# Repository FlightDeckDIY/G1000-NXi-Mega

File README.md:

### G1000-NXi-Mega

# G1000 NXi with an integrated Arduino Mega for Flight Simulators

Welcome to the G1000 NXi Mega project! This repository contains the schematic and PCB design files for a custom-built G1000 avionics panel, designed specifically for use with flight simulators like Microsoft Flight Simulator and X-Plane. Using MobiFlight to connect the G1000 hardware to your simulator of choice.

## Features
- Fully functional G1000 avionics system designed for flight simulation enthusiasts and student pilots.
- Integrated Arduino Mega for simplified connections and functionality.
- Open-source schematic and PCB designs for easy replication and modification.
- Compatible with Microsoft Flight Simulator and X-Plane.

## Getting Started
To get started with the G1000 NXi Mega:
1. Download the schematic and PCB files from the `design` folder.
2. Review the build documentation in the `docs` folder.
3. Use the included Gerber files to order PCBs from your preferred manufacturer.
4. Follow the assembly instructions to build your own G1000 avionics panel.

### Prerequisites
- Basic knowledge of electronics and PCB assembly.
- Access to a 3D printer (if building the enclosure).
- Arduino IDE and a spare Arduino for programming the Arduino Mega.

## Documentation
- **Schematics**: [View Schematics](./G1000-NXi-Mega/Frame%20PCBs)
- **3D Models**: [View Enclosure Models](https://cad.onshape.com/documents/151676533be7f9dde157788c/w/2f40da56e230263b51d6582b/e/3766505c1afa7c69551d04a4)
- **Build Guide**: Not created yet

## How to Contribute
We welcome contributions! Here's how you can get involved:
1. Fork this repository.
2. Make your changes in a new branch.
3. Submit a pull request with a description of your changes.

## License
This project is licensed under the [Creative Commons Attribution-NonCommercial 4.0 International License](https://creativecommons.org/licenses/by-nc/4.0/).

### License Summary
- **You are free to**:
  - Share — copy and redistribute the material in any medium or format.
  - Adapt — remix, transform, and build upon the material.
- **Under the following terms**:
  - Attribution — You must give appropriate credit, provide a link to the license, and indicate if changes were made.
  - NonCommercial — You may not use the material for commercial purposes.

For more details, see the full license text in the `LICENSE` file.

## Support
If you encounter any issues or have questions about the project, feel free to open an issue or contact me directly through the GitHub discussions page.

## Acknowledgments
Special thanks to the flight simulation and open-source hardware communities for their support and inspiration!

---

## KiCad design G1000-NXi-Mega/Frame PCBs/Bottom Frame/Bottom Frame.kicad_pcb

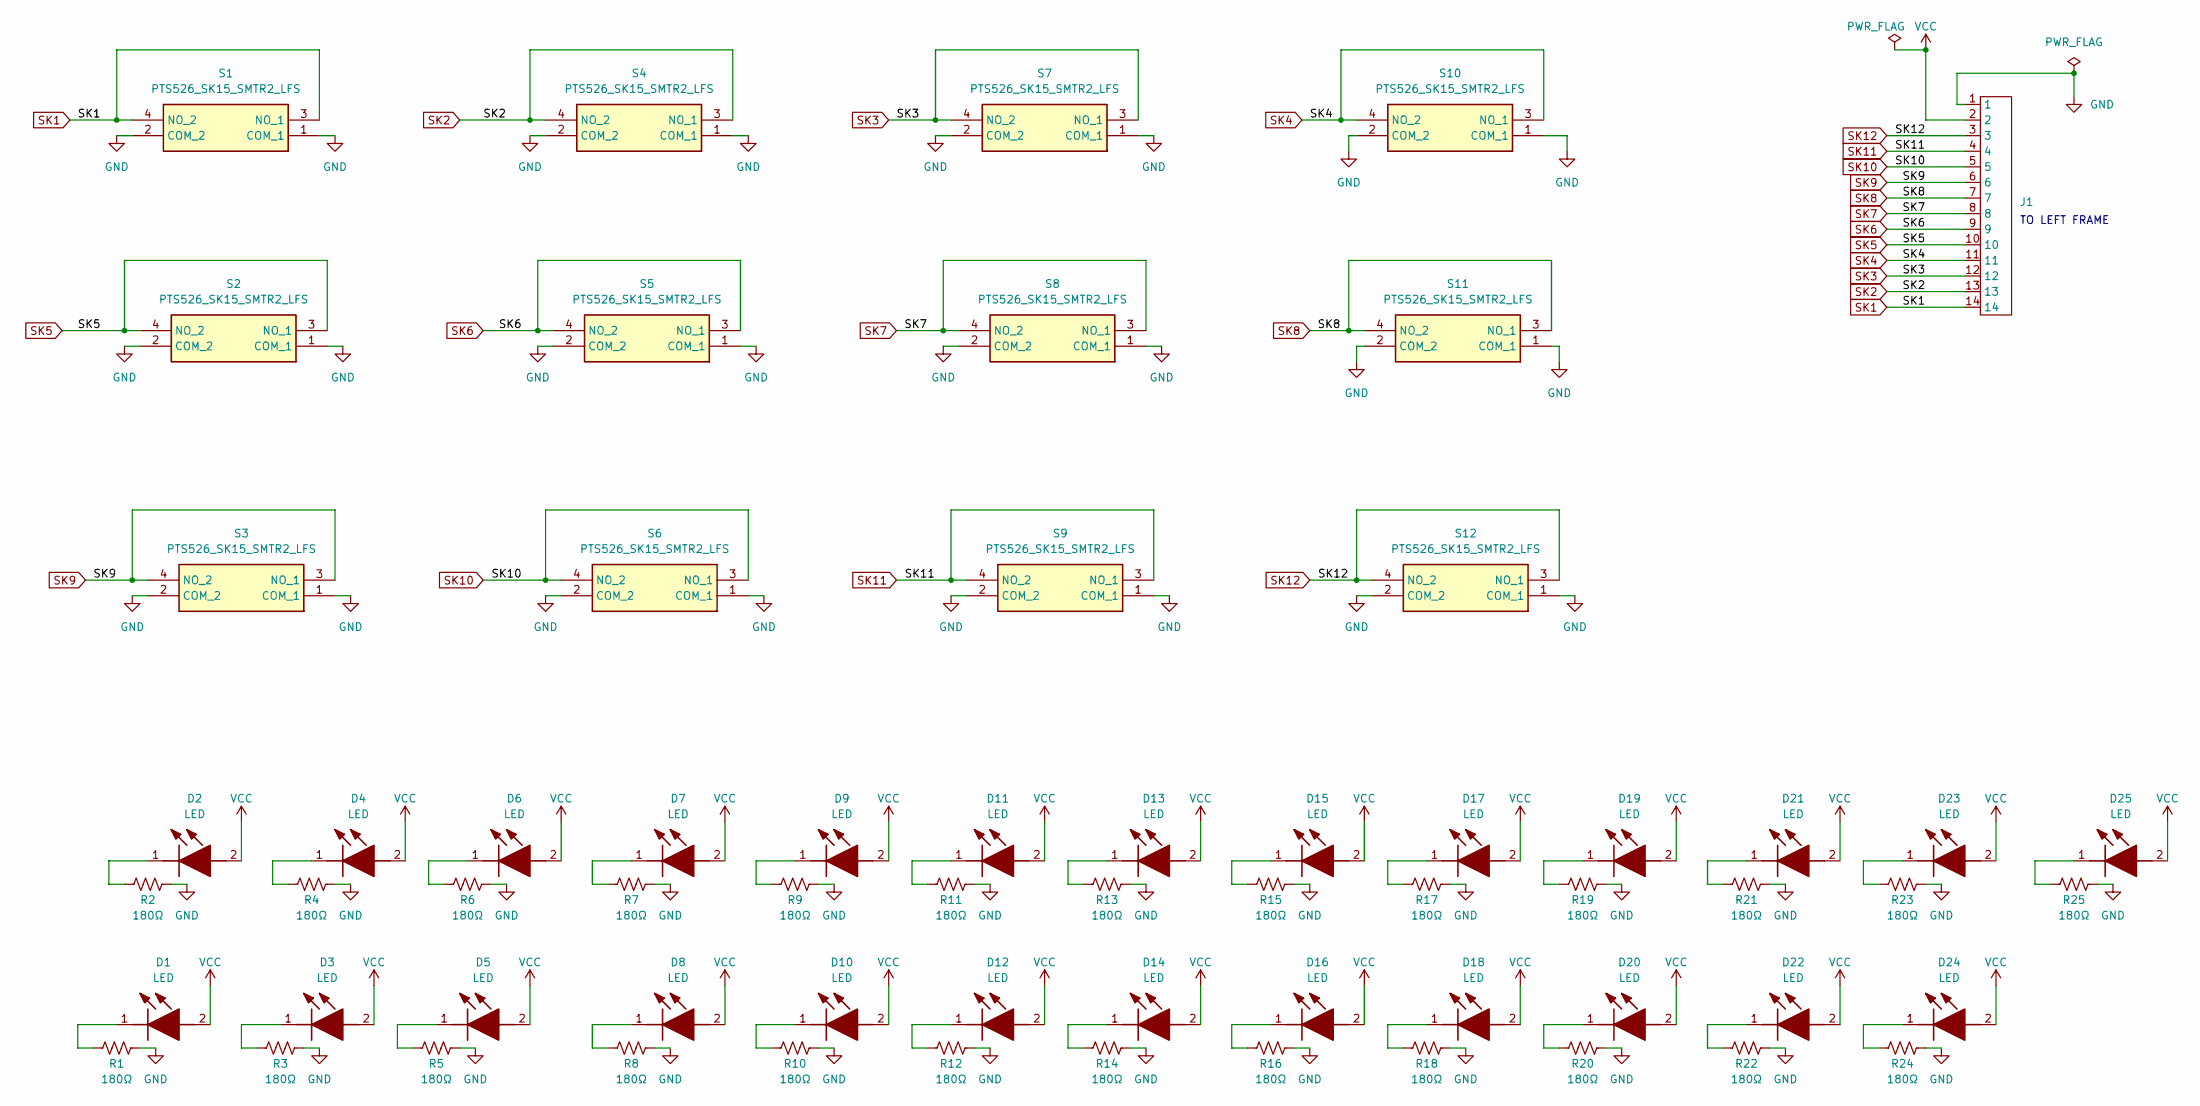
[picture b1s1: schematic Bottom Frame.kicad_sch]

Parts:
D1, D2, D3, D4, D5, D6, D7, D8, D9, D10, D11, D12, D13, D14, D15, D16, D17, D18, D19, D20, D21, D22, D23, D24, D25: LED; LEDC1608X39N; Mouser Part Number 743-IN-S63AT5UW
J1: CF31141D0R0-05-NH
R1, R2, R3, R4, R5, R6, R7, R8, R9, R10, R11, R12, R13, R14, R15, R16, R17, R18, R19, R20, R21, R22, R23, R24, R25: 180Ω; R_0603_1608Metric_Pad0.98x0.95mm_HandSolder
S1, S2, S3, S4, S5, S6, S7, S8, S9, S10, S11, S12: PTS526_SK15_SMTR2_LFS; PTS526SK15SMTR2LFS; Mouser Part Number 611-PTS526SK15SMR2L

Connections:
GND: J1.1, R1.2, R2.2, R3.2, R4.2, R5.2, R6.2, R7.2, R8.2, R9.2, R10.2, R11.2, R12.2, R13.2, R14.2, R15.2, R16.2, R17.2, R18.2, R19.2, R20.2, R21.2, R22.2, R23.2, R24.2, R25.2, S1.1 (COM_1), S1.2 (COM_2), S2.1 (COM_1), S2.2 (COM_2), S3.1 (COM_1), S3.2 (COM_2), S4.1 (COM_1), S4.2 (COM_2), S5.1 (COM_1), S5.2 (COM_2), S6.1 (COM_1), S6.2 (COM_2), S7.1 (COM_1), S7.2 (COM_2), S8.1 (COM_1), S8.2 (COM_2), S9.1 (COM_1), S9.2 (COM_2), S10.1 (COM_1), S10.2 (COM_2), S11.1 (COM_1), S11.2 (COM_2), S12.1 (COM_1), S12.2 (COM_2)
unnamed: D1.1 (K), R1.1
unnamed: D2.1 (K), R2.1
unnamed: D3.1 (K), R3.1
unnamed: D4.1 (K), R4.1
unnamed: D5.1 (K), R5.1
unnamed: D6.1 (K), R6.1
unnamed: D7.1 (K), R7.1
unnamed: D8.1 (K), R8.1
unnamed: D9.1 (K), R9.1
unnamed: D10.1 (K), R10.1
unnamed: D11.1 (K), R11.1
unnamed: D12.1 (K), R12.1
unnamed: D13.1 (K), R13.1
unnamed: D14.1 (K), R14.1
unnamed: D15.1 (K), R15.1
unnamed: D16.1 (K), R16.1
unnamed: D17.1 (K), R17.1
unnamed: D18.1 (K), R18.1
unnamed: D19.1 (K), R19.1
unnamed: D20.1 (K), R20.1
unnamed: D21.1 (K), R21.1
unnamed: D22.1 (K), R22.1
unnamed: D23.1 (K), R23.1
unnamed: D24.1 (K), R24.1
unnamed: D25.1 (K), R25.1
SK1: J1.14, S1.3 (NO_1), S1.4 (NO_2)
SK2: J1.13, S4.3 (NO_1), S4.4 (NO_2)
SK3: J1.12, S7.3 (NO_1), S7.4 (NO_2)
SK4: J1.11, S10.3 (NO_1), S10.4 (NO_2)
SK5: J1.10, S2.3 (NO_1), S2.4 (NO_2)
SK6: J1.9, S5.3 (NO_1), S5.4 (NO_2)
SK7: J1.8, S8.3 (NO_1), S8.4 (NO_2)
SK8: J1.7, S11.3 (NO_1), S11.4 (NO_2)
SK9: J1.6, S3.3 (NO_1), S3.4 (NO_2)
SK10: J1.5, S6.3 (NO_1), S6.4 (NO_2)
SK11: J1.4, S9.3 (NO_1), S9.4 (NO_2)
SK12: J1.3, S12.3 (NO_1), S12.4 (NO_2)
VCC: D1.2 (A), D2.2 (A), D3.2 (A), D4.2 (A), D5.2 (A), D6.2 (A), D7.2 (A), D8.2 (A), D9.2 (A), D10.2 (A), D11.2 (A), D12.2 (A), D13.2 (A), D14.2 (A), D15.2 (A), D16.2 (A), D17.2 (A), D18.2 (A), D19.2 (A), D20.2 (A), D21.2 (A), D22.2 (A), D23.2 (A), D24.2 (A), D25.2 (A), J1.2

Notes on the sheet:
TO LEFT FRAME

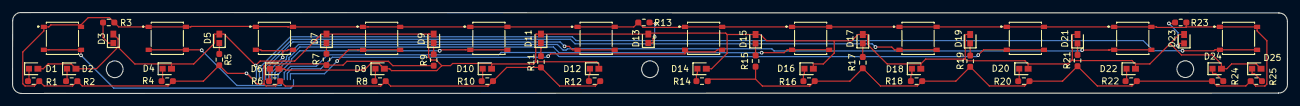
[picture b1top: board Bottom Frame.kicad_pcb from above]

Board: 2 copper layers, 206.0 x 13.1 mm, 66 parts (1 on the bottom side), 39 nets.

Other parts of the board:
C: MountingHole_2.7mm_M2.5
L: MountingHole_2.7mm_M2.5
R: MountingHole_2.7mm_M2.5

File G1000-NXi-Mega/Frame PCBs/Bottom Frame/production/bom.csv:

Designator,Footprint,Quantity,Value,LCSC Part #
"D1, D10, D11, D12, D13, D14, D15, D16, D17, D18, D19, D2, D20, D21, D22, D23, D24, D25, D3, D4, D5, D6, D7, D8, D9",LEDC1608X39N,25,LED,
J1,CF31141D0R0-05-NH,1,~,
"R1, R10, R11, R12, R13, R14, R15, R16, R17, R18, R19, R2, R20, R21, R22, R23, R24, R25, R3, R4, R5, R6, R7, R8, R9",0603,25,180Ω,
"S1, S10, S11, S12, S2, S3, S4, S5, S6, S7, S8, S9",PTS526SK15SMTR2LFS,12,PTS526_SK15_SMTR2_LFS,

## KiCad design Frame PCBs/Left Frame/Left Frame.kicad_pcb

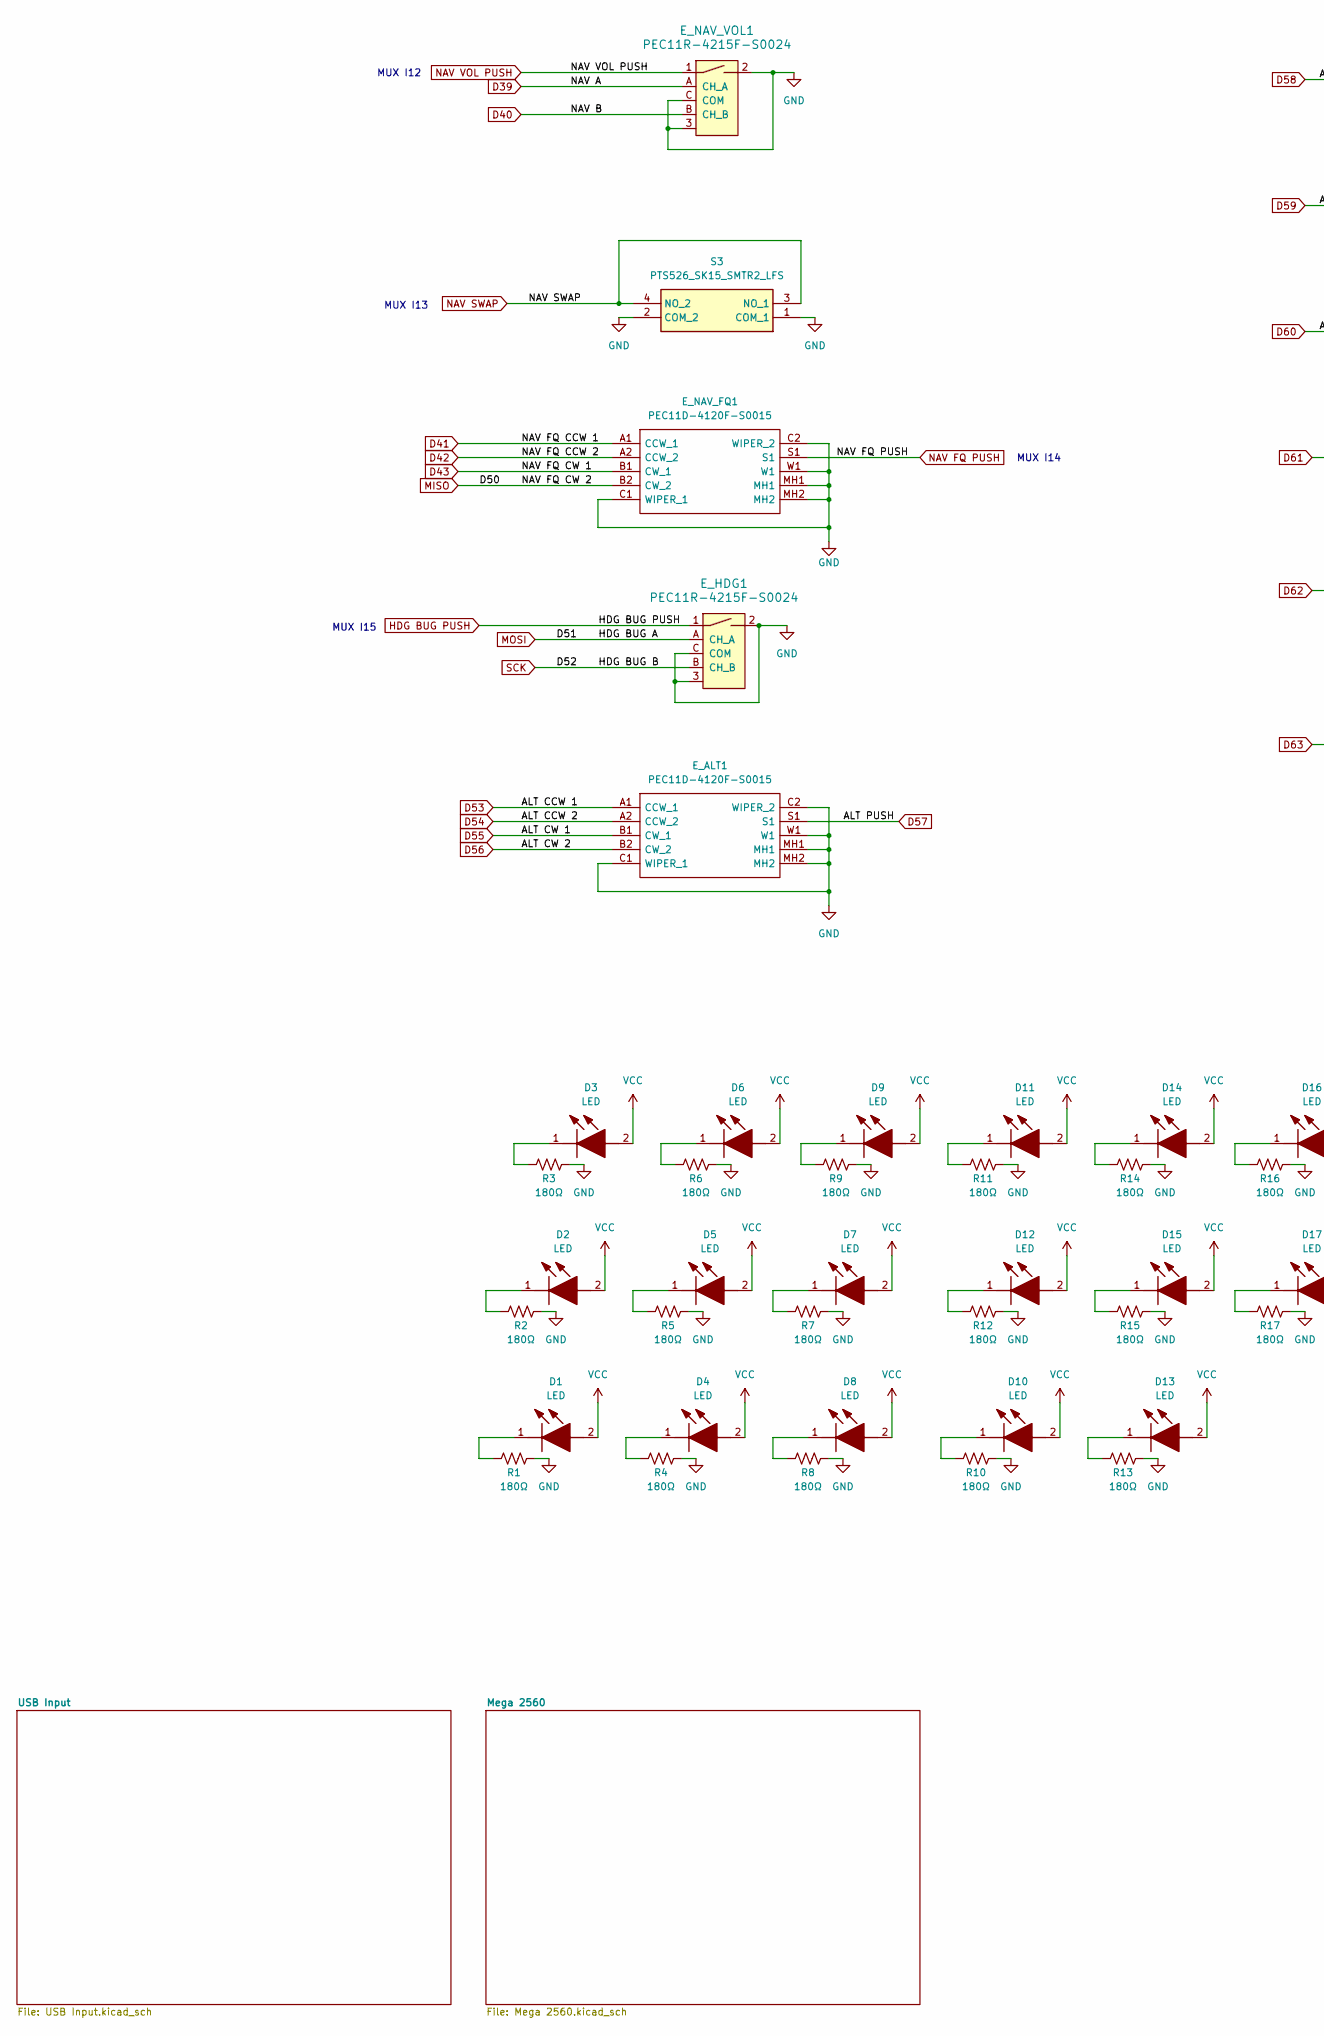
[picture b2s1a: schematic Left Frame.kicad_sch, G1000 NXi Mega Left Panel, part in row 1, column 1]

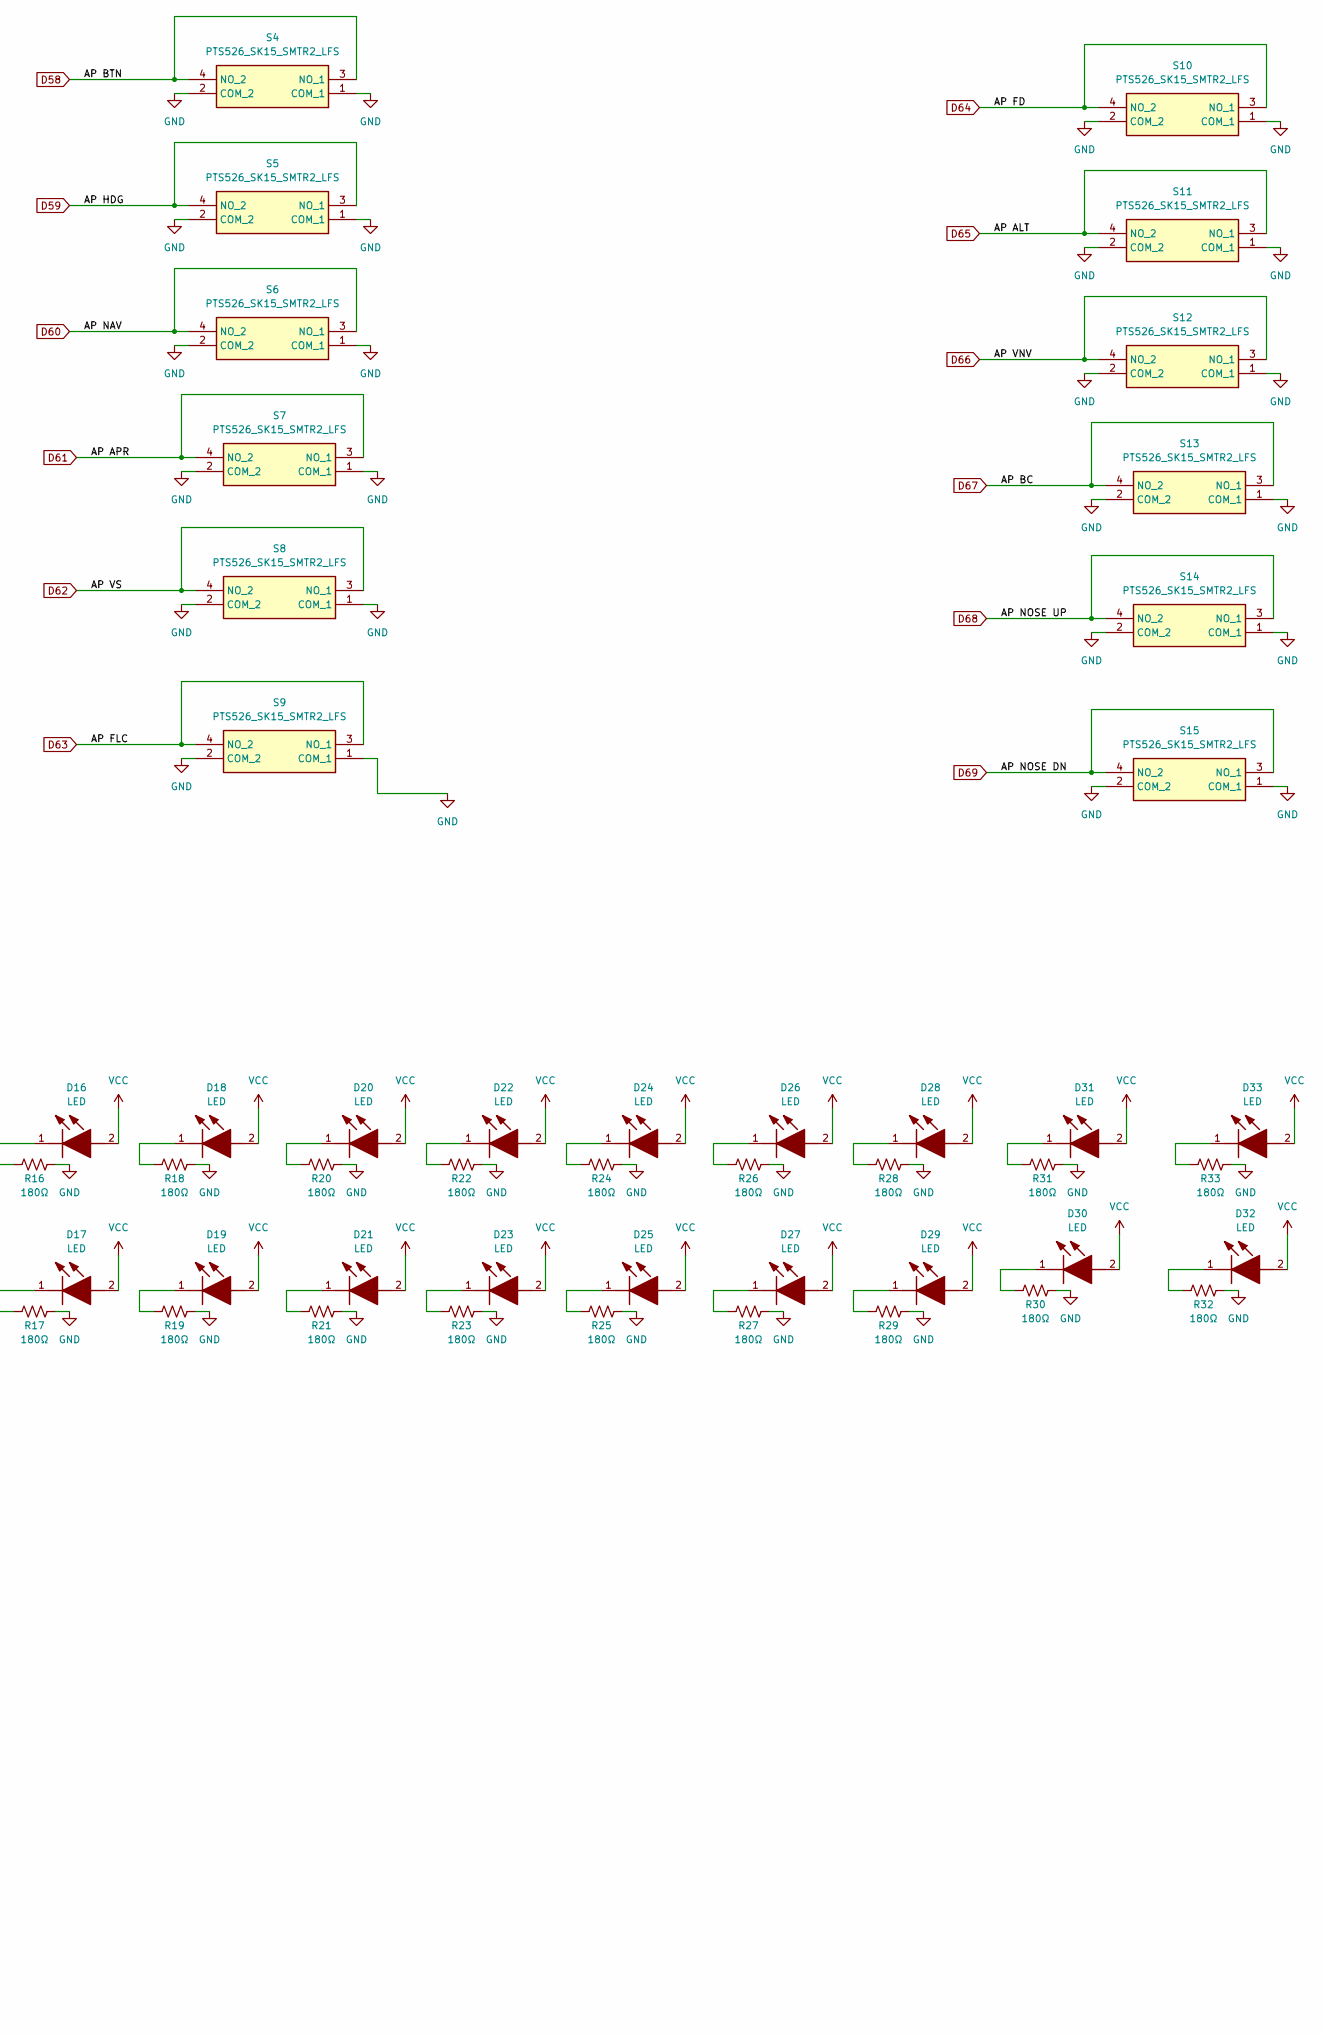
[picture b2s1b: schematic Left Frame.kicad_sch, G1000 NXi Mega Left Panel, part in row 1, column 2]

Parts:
D1, D2, D3, D4, D5, D6, D7, D8, D9, D10, D11, D12, D13, D14, D15, D16, D17, D18, D19, D20, D21, D22, D23, D24, D25, D26, D27, D28, D29, D30, D31, D32, D33: LED; LEDC1608X39N; Mouser Part Number 743-IN-S63AT5UW
E_ALT1: PEC11D-4120F-S0015; PEC11D4120FS0015; Mouser Part Number 652-PEC11D4120FS0015
E_HDG1: PEC11R-4215F-S0024; Rotary_Encoder_Switched_PEC11R; MPN PEC11R-4215F-S0024; Digi-Key_PN PEC11R-4215F-S0024-ND
E_NAV_FQ1: PEC11D-4120F-S0015; PEC11D4120FS0015; Mouser Part Number 652-PEC11D4120FS0015
E_NAV_VOL1: PEC11R-4215F-S0024; Rotary_Encoder_Switched_PEC11R; MPN PEC11R-4215F-S0024; Digi-Key_PN PEC11R-4215F-S0024-ND
R1, R2, R3, R4, R5, R6, R7, R8, R9, R10, R11, R12, R13, R14, R15, R16, R17, R18, R19, R20, R21, R22, R23, R24, R25, R26, R27, R28, R29, R30, R31, R32, R33: 180Ω; R_0603_1608Metric_Pad0.98x0.95mm_HandSolder
S3, S4, S5, S6, S7, S8, S9, S10, S11, S12, S13, S14, S15: PTS526_SK15_SMTR2_LFS; PTS526SK15SMTR2LFS; Mouser Part Number 611-PTS526SK15SMR2L

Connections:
D39: E_NAV_VOL1.A (CH_A); also elsewhere on the board
D40: E_NAV_VOL1.B (CH_B); also elsewhere on the board
D41: E_NAV_FQ1.A1 (CCW_1); also elsewhere on the board
D42: E_NAV_FQ1.A2 (CCW_2); also elsewhere on the board
D43: E_NAV_FQ1.B1 (CW_1); also elsewhere on the board
D53: E_ALT1.A1 (CCW_1); also elsewhere on the board
D54: E_ALT1.A2 (CCW_2); also elsewhere on the board
D55: E_ALT1.B1 (CW_1); also elsewhere on the board
D56: E_ALT1.B2 (CW_2); also elsewhere on the board
D57: E_ALT1.S1; also elsewhere on the board
D58: S4.3 (NO_1), S4.4 (NO_2); also elsewhere on the board
D59: S5.3 (NO_1), S5.4 (NO_2); also elsewhere on the board
D60: S6.3 (NO_1), S6.4 (NO_2); also elsewhere on the board
D61: S7.3 (NO_1), S7.4 (NO_2); also elsewhere on the board
D62: S8.3 (NO_1), S8.4 (NO_2); also elsewhere on the board
D63: S9.3 (NO_1), S9.4 (NO_2); also elsewhere on the board
D64: S10.3 (NO_1), S10.4 (NO_2); also elsewhere on the board
D65: S11.3 (NO_1), S11.4 (NO_2); also elsewhere on the board
D66: S12.3 (NO_1), S12.4 (NO_2); also elsewhere on the board
D67: S13.3 (NO_1), S13.4 (NO_2); also elsewhere on the board
D68: S14.3 (NO_1), S14.4 (NO_2); also elsewhere on the board
D69: S15.3 (NO_1), S15.4 (NO_2); also elsewhere on the board
GND: E_ALT1.C1 (WIPER_1), E_ALT1.C2 (WIPER_2), E_ALT1.MH1, E_ALT1.MH2, E_ALT1.W1, E_HDG1.2, E_HDG1.3, E_HDG1.C (COM), E_NAV_FQ1.C1 (WIPER_1), E_NAV_FQ1.C2 (WIPER_2), E_NAV_FQ1.MH1, E_NAV_FQ1.MH2, E_NAV_FQ1.W1, E_NAV_VOL1.2, E_NAV_VOL1.3, E_NAV_VOL1.C (COM), R1.2, R2.2, R3.2, R4.2, R5.2, R6.2, R7.2, R8.2, R9.2, R10.2, R11.2, R12.2, R13.2, R14.2, R15.2, R16.2, R17.2, R18.2, R19.2, R20.2, R21.2, R22.2, R23.2, R24.2, R25.2, R26.2, R27.2, R28.2, R29.2, R30.2, R31.2, R32.2, R33.2, S3.1 (COM_1), S3.2 (COM_2), S4.1 (COM_1), S4.2 (COM_2), S5.1 (COM_1), S5.2 (COM_2), S6.1 (COM_1), S6.2 (COM_2), S7.1 (COM_1), S7.2 (COM_2), S8.1 (COM_1), S8.2 (COM_2), S9.1 (COM_1), S9.2 (COM_2), S10.1 (COM_1), S10.2 (COM_2), S11.1 (COM_1), S11.2 (COM_2), S12.1 (COM_1), S12.2 (COM_2), S13.1 (COM_1), S13.2 (COM_2), S14.1 (COM_1), S14.2 (COM_2), S15.1 (COM_1), S15.2 (COM_2); also elsewhere on the board
HDG BUG PUSH: E_HDG1.1; also elsewhere on the board
MISO: E_NAV_FQ1.B2 (CW_2); also elsewhere on the board
MOSI: E_HDG1.A (CH_A); also elsewhere on the board
NAV FQ PUSH: E_NAV_FQ1.S1; also elsewhere on the board
NAV SWAP: S3.3 (NO_1), S3.4 (NO_2); also elsewhere on the board
NAV VOL PUSH: E_NAV_VOL1.1; also elsewhere on the board
unnamed: D1.1 (K), R1.1
unnamed: D2.1 (K), R2.1
unnamed: D3.1 (K), R3.1
unnamed: D4.1 (K), R4.1
unnamed: D5.1 (K), R5.1
unnamed: D6.1 (K), R6.1
unnamed: D7.1 (K), R7.1
unnamed: D8.1 (K), R8.1
unnamed: D9.1 (K), R9.1
unnamed: D10.1 (K), R10.1
unnamed: D11.1 (K), R11.1
unnamed: D12.1 (K), R12.1
unnamed: D13.1 (K), R13.1
unnamed: D14.1 (K), R14.1
unnamed: D15.1 (K), R15.1
unnamed: D16.1 (K), R16.1
unnamed: D17.1 (K), R17.1
unnamed: D18.1 (K), R18.1
unnamed: D19.1 (K), R19.1
unnamed: D20.1 (K), R20.1
unnamed: D21.1 (K), R21.1
unnamed: D22.1 (K), R22.1
unnamed: D23.1 (K), R23.1
unnamed: D24.1 (K), R24.1
unnamed: D25.1 (K), R25.1
unnamed: D26.1 (K), R26.1
unnamed: D27.1 (K), R27.1
unnamed: D28.1 (K), R28.1
unnamed: D29.1 (K), R29.1
unnamed: D30.1 (K), R30.1
unnamed: D31.1 (K), R31.1
unnamed: D32.1 (K), R32.1
unnamed: D33.1 (K), R33.1
SCK: E_HDG1.B (CH_B); also elsewhere on the board
VCC: D1.2 (A), D2.2 (A), D3.2 (A), D4.2 (A), D5.2 (A), D6.2 (A), D7.2 (A), D8.2 (A), D9.2 (A), D10.2 (A), D11.2 (A), D12.2 (A), D13.2 (A), D14.2 (A), D15.2 (A), D16.2 (A), D17.2 (A), D18.2 (A), D19.2 (A), D20.2 (A), D21.2 (A), D22.2 (A), D23.2 (A), D24.2 (A), D25.2 (A), D26.2 (A), D27.2 (A), D28.2 (A), D29.2 (A), D30.2 (A), D31.2 (A), D32.2 (A), D33.2 (A); also elsewhere on the board

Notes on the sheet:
MUX I14
MUX I12
MUX I15
MUX I13

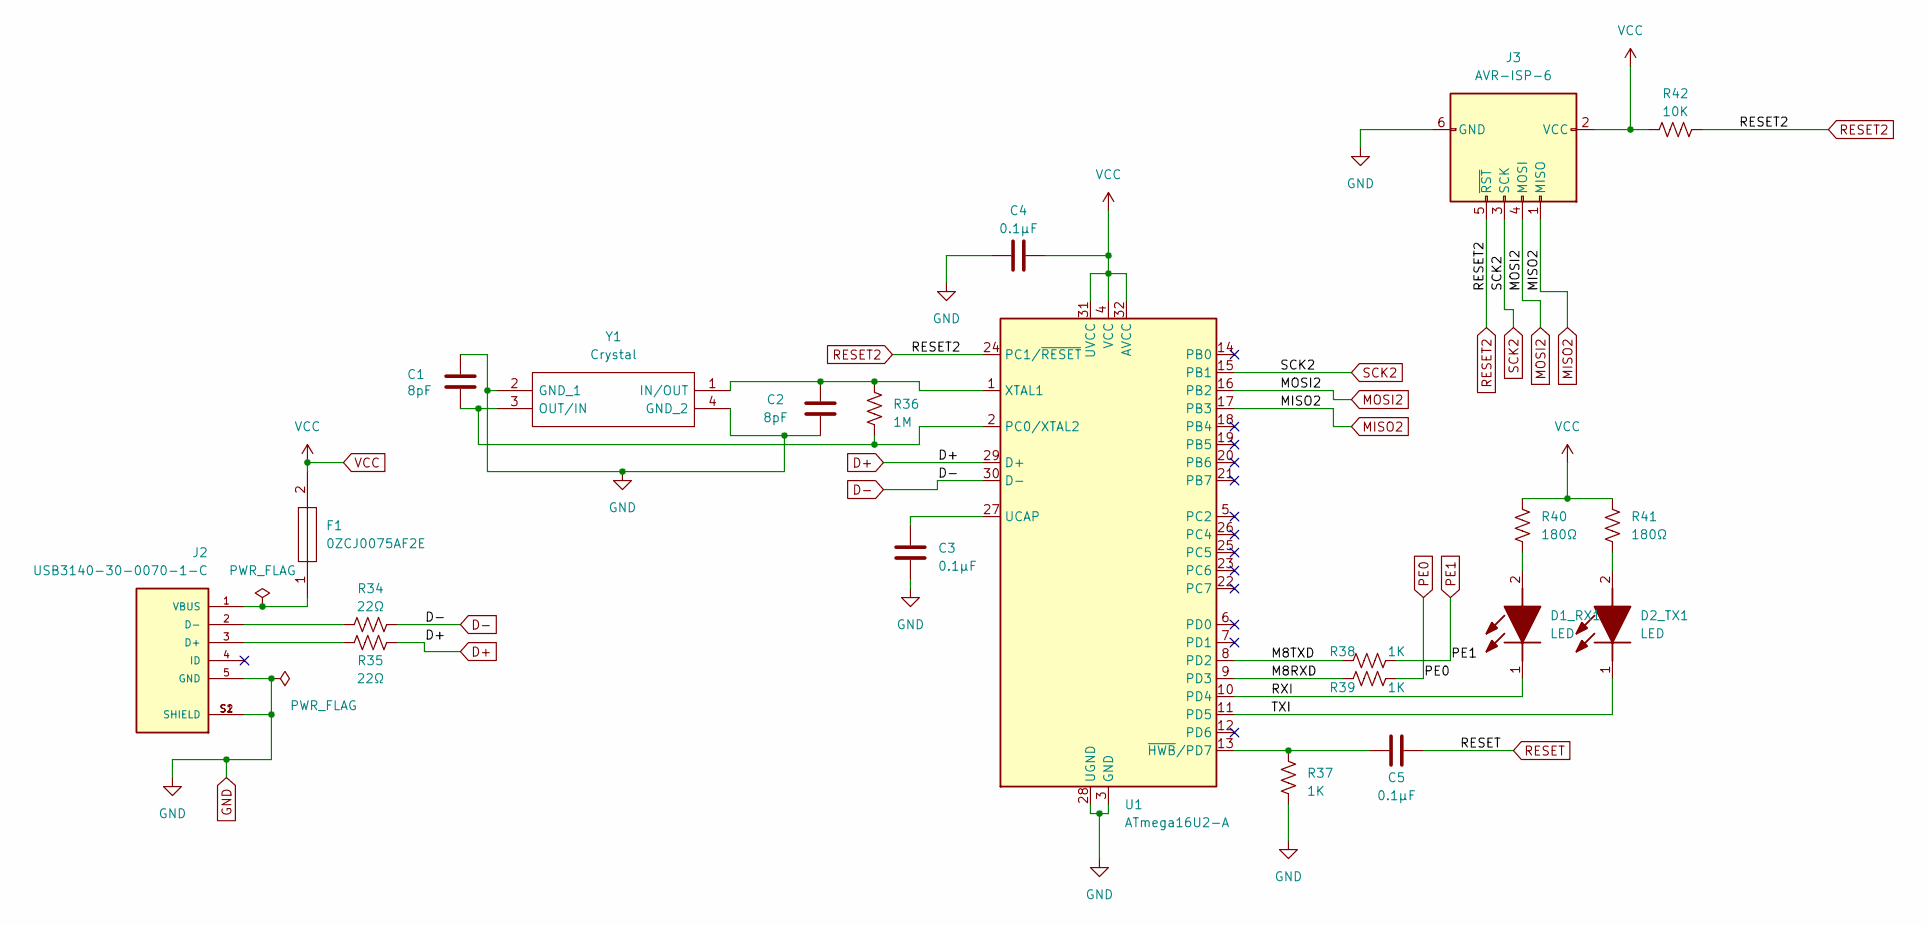
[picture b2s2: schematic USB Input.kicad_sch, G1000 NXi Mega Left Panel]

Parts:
C1, C2: 8pF; C_0603_1608Metric_Pad1.08x0.95mm_HandSolder
C3, C4, C5: 0.1µF; C_0603_1608Metric_Pad1.08x0.95mm_HandSolder
D1_RX1, D2_TX1: LED; LEDC1608X39N; Mouser Part Number 743-IN-S63AT5UW
F1: 0ZCJ0075AF2E; FUSC3216X125N; Mouser Part Number 530-0ZCJ0075AF2E
J2: USB3140-30-0070-1-C; GCT_USB3140-30-0070-1-C_REVE1; Mouser Part Number 640-USB31403000701C
J3: AVR-ISP-6; PinHeader_2x03_P2.54mm_Vertical_SMD
R34, R35: 22Ω; R_0603_1608Metric_Pad0.98x0.95mm_HandSolder
R36: 1M; R_0603_1608Metric_Pad0.98x0.95mm_HandSolder
R37, R38, R39: 1K; R_0603_1608Metric_Pad0.98x0.95mm_HandSolder
R40, R41: 180Ω; R_0603_1608Metric_Pad0.98x0.95mm_HandSolder
R42: 10K; R_0603_1608Metric_Pad0.98x0.95mm_HandSolder
U1: ATmega16U2-A; TQFP-32_7x7mm_P0.8mm
Y1: Crystal; ECS160836B2CKMTR; Mouser Part Number 520-160-8-36B2-CKMTR

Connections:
/USB Input/M8RXD: R39.2, U1.9 (PD3)
/USB Input/M8TXD: R38.1, U1.8 (PD2)
/USB Input/RXI: D1_RX1.1 (K), U1.10 (PD4)
/USB Input/TXI: D2_TX1.1 (K), U1.11 (PD5)
D+: R35.2, U1.29 (D+)
D-: R34.2, U1.30 (D-)
GND: C1.2, C2.1, C3.2, C4.1, J2.5 (GND), J2.S1 (SHIELD), J2.S2 (SHIELD), J3.6 (GND), R37.2, U1.3 (GND), U1.28 (UGND), Y1.2 (GND_1), Y1.4 (GND_2); also elsewhere on the board
MISO2: J3.1 (MISO), U1.17 (PB3)
MOSI2: J3.4 (MOSI), U1.16 (PB2)
unnamed: D1_RX1.2 (A), R40.2
unnamed: D2_TX1.2 (A), R41.2
unnamed: J2.3 (D+), R35.1
unnamed: J2.2 (D-), R34.1
unnamed: F1.1, J2.1 (VBUS)
unnamed: C1.1, R36.2, U1.2 (PC0/XTAL2), Y1.3 (OUT/IN)
unnamed: C3.1, U1.27 (UCAP)
unnamed: C2.2, R36.1, U1.1 (XTAL1), Y1.1 (IN/OUT)
unnamed: C5.1, R37.1, U1.13 (~HWB/PD7)
PE0: R39.1; also elsewhere on the board
PE1: R38.2; also elsewhere on the board
RESET: C5.2; also elsewhere on the board
RESET2: J3.5 (~RST), R42.2, U1.24 (PC1/~RESET)
SCK2: J3.3 (SCK), U1.15 (PB1)
VCC: C4.2, F1.2, J3.2 (VCC), R40.1, R41.1, R42.1, U1.4 (VCC), U1.31 (UVCC), U1.32 (AVCC); also elsewhere on the board

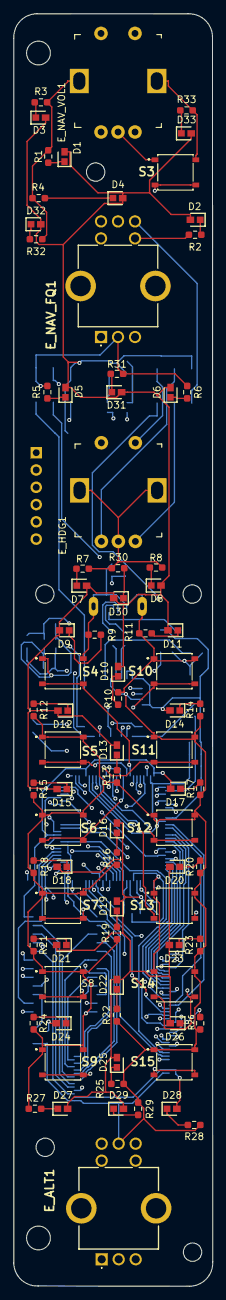
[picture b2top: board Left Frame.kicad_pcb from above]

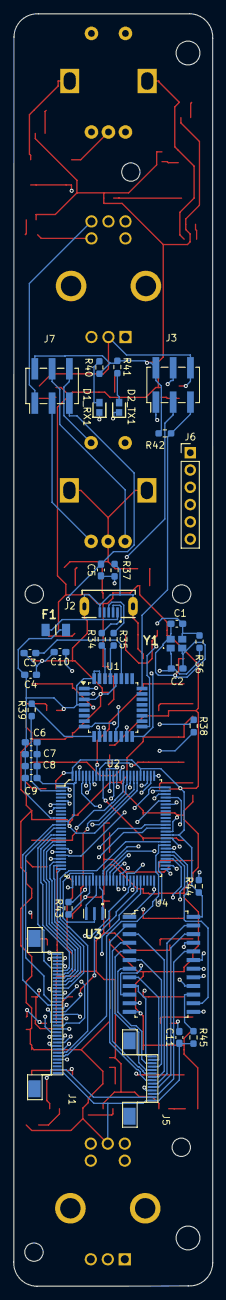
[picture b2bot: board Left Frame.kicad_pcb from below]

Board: 4 copper layers, 29.3 x 187.1 mm, 127 parts (37 on the bottom side), 145 nets.

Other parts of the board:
C6, C7, C8, C9, C10, C11: 0.1µF; C_0603_1608Metric_Pad1.08x0.95mm_HandSolder
J1: CF31361D0R0-05-NH
J5: CF31141D0R0-05-NH
J6: Conn_01x06_Pin; PinHeader_1x06_P2.54mm_Vertical
J7: AVR-ISP-6; PinHeader_2x03_P2.54mm_Vertical_SMD
PCBMount1, PCBMount2, PCBMount3, PCBMount4, PCBMount5: MountingHole_2.7mm_M2.5
R43, R44, R45: 10K; R_0603_1608Metric_Pad0.98x0.95mm_HandSolder
REF1, REF2: MountingHole_3.5mm
U2: ATMEGA2560-16AU; TQFP-100_14x14mm
U3: CSTNE16M0V530000R0
U4: CD74HC4067SM96; SSOP-24_W5.30mm

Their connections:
D2: J1.1, U2.6 (PE4(OC3B/INT4))
D3: J1.2, U2.7 (PE5(OC3C/INT5))
D4: J1.3, U2.1 (PG5(OC08))
D5: J1.4, U2.5 (PE3(OC3A/AIN1))
D6: J1.5, U2.15 (PH3(OC4A))
D7: J1.6, U2.16 (PH4(OC4B))
D8: J1.7, U2.17 (PH5(OC4C))
D9: J1.8, U2.18 (PH6(OC2B))
D10: J1.9, U2.23 (PB4(OC2A/PCINT4))
D11: J1.10 (f), U2.24 (PB5(OC1A/PCINT5))
D12: J1.11, U2.25 (PB6(OC1B/PCINT6))
D13: J1.12, U2.26 (PB7(OC0A/OC1C/PCINT7))
D14: J1.13, U2.64 (PJ1(TXD3/PCINT10))
D15: J1.14, U2.63 (PJ0(RXD3/PCINT9))
D16: J1.15, U2.13 (PH1(TXD2))
D17: J1.16, U2.12 (PH0(RXD2))
D18: J1.17, U2.46 (PD3(TXD1/INT3))
D19: J1.18, U2.45 (PD2(RXD1/INT2))
D20: J1.19, U2.44 (PD1(SDA/INT1))
D21: J1.20, U2.43 (PD0(SCL/INT0))
D22: J1.21, U2.78 (PA0(AD0))
D23: J1.22, U2.77 (PA1(AD1))
D24: J1.23, U2.76 (PA2(AD2))
D25: J1.24, U2.75 (PA3(AD3))
D26: J1.25, U2.74 (PA4(AD4))
D27: J1.26, U2.73 (PA5(AD5))
D28: J1.27, U2.72 (PA6(AD6))
D29: J1.28, U2.71 (PA7(AD7))
D30: J1.29, U2.60 (PC7(A15))
D31: J1.30, U2.59 (PC6(A14))
D32: J1.31, U2.58 (PC5(A13))
D33: J1.32, U2.57 (PC4(A12))
D34: U2.56 (PC3(A11)), U4.14 (S2)
D35: U2.55 (PC2(A10)), U4.13 (S3)
D36: U2.54 (PC1(A9)), U4.11 (S1)
D37: U2.53 (PC0(A8)), U4.10 (S0)
D38: R44.2, U2.50 (PD7(T0)), U4.1 (COM)
D39: U2.70 (PG2(ALE)); also elsewhere on the board
D40: U2.52 (PG1(~RD)); also elsewhere on the board
D41: U2.51 (PG0(~WR)); also elsewhere on the board
D42: U2.42 (PL7); also elsewhere on the board
D43: U2.41 (PL6); also elsewhere on the board
D44: J6.1, U2.40 (PL5(OC5C))
D45: J6.2, U2.39 (PL4(OC5B))
D46: J6.3, U2.38 (PL3(OC5A))
D47: J6.4, U2.37 (PL2(T5))
D48: J6.5, U2.36 (PL1(ICP5))
D49: J6.6, U2.35 (PL0(ICP4))
D53: U2.19 (PB0(~SS/PCINT0)); also elsewhere on the board
D54: U2.97 (PF0(ADC0)); also elsewhere on the board
D55: U2.96 (PF1(ADC1)); also elsewhere on the board
D56: U2.95 (PF2(ADC2)); also elsewhere on the board
D57: U2.94 (PF3(ADC3)); also elsewhere on the board
D58: U2.93 (PF4(ADC4/TCK)); also elsewhere on the board
D59: U2.92 (PF5(ADC5/TMS)); also elsewhere on the board
D60: U2.91 (PF6(ADC6/TDO)); also elsewhere on the board
D61: U2.90 (PF7(ADC7/TDI)); also elsewhere on the board
D62: U2.89 (PK0(ADC8/PCINT16)); also elsewhere on the board
D63: U2.88 (PK1(ADC9/PCINT17)); also elsewhere on the board
D64: U2.87 (PK2(ADC10/PCINT18)); also elsewhere on the board
D65: U2.86 (PK3(ADC11/PCINT19)); also elsewhere on the board
D66: U2.85 (PK4(ADC12/PCINT20)); also elsewhere on the board
D67: U2.84 (PK5(ADC13/PCINT21)); also elsewhere on the board
D68: U2.83 (PK6(ADC14/PCINT22)); also elsewhere on the board
D69: U2.82 (PK7(ADC15/PCINT23)); also elsewhere on the board
GND: C6.2, C7.2, C8.2, C9.2, C10.2, C11.1, J1.36, J5.14, J7.6 (GND), R45.2, U2.11 (GND), U2.32 (GND), U2.62 (GND), U2.81 (GND), U2.99 (GND), U3.2 (GND), U4.12 (GND); also elsewhere on the board
HDG BUG PUSH: U4.16 (I15); also elsewhere on the board
MISO: J7.1 (MISO), U2.22 (PB3(MISO/PCINT3)); also elsewhere on the board
MOSI: J7.4 (MOSI), U2.21 (PB2(MOSI/PCINT2)); also elsewhere on the board
NAV FQ PUSH: U4.17 (I14); also elsewhere on the board
NAV SWAP: U4.18 (I13); also elsewhere on the board
NAV VOL PUSH: U4.19 (I12); also elsewhere on the board
unnamed: C10.1, U2.98 (AREF)
unnamed: U2.34 (XTAL1), U3.1 (INPUT)
unnamed: U2.33 (XTAL2), U3.3 (OUTPUT)
unnamed: R45.1, U4.15 (E)
PE0: U2.2 (PE0(RXD0/PCINT8)); also elsewhere on the board
PE1: U2.3 (PE1(TXD0)); also elsewhere on the board
RESET: J7.5 (~RST), R43.2, U2.30 (~RESET); also elsewhere on the board
SCK: J7.3 (SCK), U2.20 (PB1(SCK/PCINT1)); also elsewhere on the board
SK1: J5.1, U4.9 (I0)
SK2: J5.2, U4.8 (I1)
SK3: J5.3, U4.7 (I2)
SK4: J5.4, U4.6 (I3)
SK5: J5.5, U4.5 (I4)
SK6: J5.6, U4.4 (I5)
SK7: J5.7, U4.3 (I6)
SK8: J5.8, U4.2 (I7)
SK9: J5.9, U4.23 (I8)
SK10: J5.10, U4.22 (I9)
SK11: J5.11, U4.21 (I10)
SK12: J5.12, U4.20 (I11)
VCC: C6.1, C7.1, C8.1, C9.1, C11.2, J1.35, J5.13, J7.2 (VCC), R43.1, R44.1, U2.10 (VCC), U2.31 (VCC), U2.61 (VCC), U2.80 (VCC), U2.100 (AVCC), U4.24 (VCC); also elsewhere on the board

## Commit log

2024-12-10 Create LICENSE
2024-12-10 Add .gitignore
2024-12-10 Add KiCad projects & files
2024-12-10 Move files
2024-12-10 Add Frame PCBs directory
2024-12-10 Update submodule to include Frame PCBs
2024-12-10 Reorganize repository structure
2024-12-10 Remove empty .gitmodules file
2024-12-10 Moved folders
2025-02-03 Fix README.md
2025-02-03 Fix broken links in README.md
2025-02-08 Remove old version zip files
